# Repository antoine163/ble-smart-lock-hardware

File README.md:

# Bluetooth LE Smart Lock - Hardware

## Cartes électronique
Ce dépôt contient deux cartes :
- **[BleSmartLock](BleSmartLock/README.md)**: La carte principale, construite autour du bluenrg-m2, inclut toute l'électronique de contrôle pour la serrure.
- **[LightSensor](LightSensor/README.md)**: Cette carte contient le capteur de lumière, permettant de le placer à distance. Cette carte est optionnelle.

## Réalisation

### Liste du matérielle:
Cette liste de matériel est disponible sur Amazon.
- [Alimentation 12V](https://www.amazon.fr/dp/B0924XBMCF?ref=ppx_yo2ov_dt_b_fed_asin_title&th=1) pour alimenter la serrure.
- [Serrure électromécanique](https://www.amazon.fr/dp/B07KWMH16C?ref=ppx_yo2ov_dt_b_fed_asin_title) pour la partie électromécanique de la serrure.
- [Bouton lumineux](https://www.amazon.fr/dp/B0CBRFQLLT?ref=ppx_yo2ov_dt_b_fed_asin_title&th=1) pour l'ouverture de la serrure et visualisation de l'état de la serrure.
- [Boîtier étanche](https://www.amazon.fr/dp/B09V7M8759?ref=ppx_yo2ov_dt_b_fed_asin_title) pour recevoir la carte électronique principale *BleSmartLock*.
- [Câble 4 conducteurs](https://www.amazon.fr/dp/B0BFWJ19YJ?ref=ppx_yo2ov_dt_b_fed_asin_title&th=1) pour la connexion entre la carte électronique principale et:
    - La serrure électromécanique
    - Le bouton lumineux
    - L'éclairage d'ambiance
    - Le capteur de lumière
    - L'éclairage extérieur
- [Câble 2 conducteurs](https://www.amazon.fr/dp/B0B7WV1QCW?ref=ppx_yo2ov_dt_b_fed_asin_title) pour l'alimentation.
- [Presse-étoupes](https://www.amazon.fr/dp/B07V7F5HKQ?ref=ppx_yo2ov_dt_b_fed_asin_title&th=1) pour faire passer les différents câbles dans les boîtiers étanches.
- [Boîtier étanche](https://www.amazon.fr/dp/B0BZCS1PN1?ref=ppx_yo2ov_dt_b_fed_asin_title) pour recevoir le capteur de luminosité *LightSensor* et la lampe extérieur *Mini-Light*.
- [Colle epoxy transparent](https://www.amazon.fr/dp/B07JL8JC3N?ref=ppx_yo2ov_dt_b_fed_asin_title) pour réaliser une vitre dans le boîtier du capteur de luminosité et de la lampe extérieur.

### Mise en boiter de la carte principal *BleSmartLock* 

### Mise en boiter de la carte capteur *LightSensor* et lampe extérieur *Mini-Light*
On notera ici que 2 cartes *Mini-Light* ont été utilisées pour augmenter la luminosité de la lampe extérieur.  
**NOTE:** Un maximum de 2 cartes *Mini-Light* peut être utilisé directement à la carte principale *BleSmartLock*.  

Au préalable, il est nécessaire de percer un trou rectangulaire et un trou rond dans le couvercle du boîtier, puis de les remplir de colle époxy transparente. Cela permet de créer des vitres, assurant ainsi le passage de la lumière utile au capteur de luminosité et d'éclairage extérieur.  

## Prototypes
### Avec les cartes v1.0

### Sur plaque d'essai

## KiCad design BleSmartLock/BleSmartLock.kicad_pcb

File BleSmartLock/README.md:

# BleSmartLock Board
Cette carte est la carte principale du projet. Elle est basée sur le module radio Bluenrg-m2 et fais l'interface avec les autres organes, telle que la serrure elle-même et le bouton pour l'ouverture.

Voir le [README](../../Firmware/README.md) du firmware pour la programmation de cette carte.

## Vue 3D

## Réalisation
### Fabrication de la version v1.0
#### Correction
Une erreur c'est glissée à la saisie de la schématique. DIO12 peut seulement être une entrée. la version v1.1 inverse DIO12 avec DIO6.
Il faut inverser c'est deux gpio sur le pcb en coupent deux pistes et en croisent les connections.

#### Photos

#### BOM
La bom interactive est trouvable [ici](https://antoine163.github.io/ble-smart-lock-hardware/Ble_Smart_Lock_1.0-ibom.html). 

### Fabrication de la version v1.1
Je n'est pas fabrique cette version, mais elle dispose exactement des mêmes composent que la v1.0.
La bom interactive est trouvable [ici](https://antoine163.github.io/ble-smart-lock-hardware/Ble%20Smart%20Lock-1.1-ibom.html). 

# Schématique

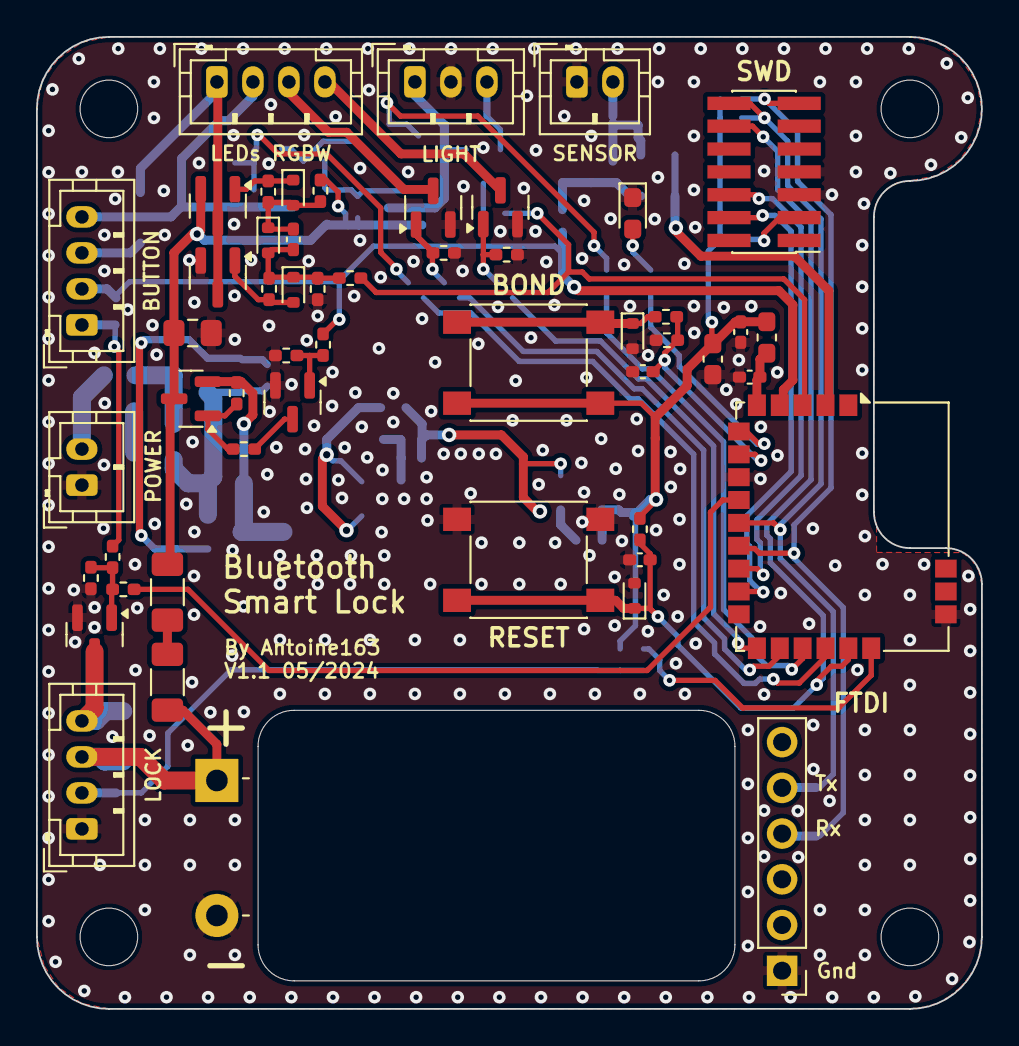
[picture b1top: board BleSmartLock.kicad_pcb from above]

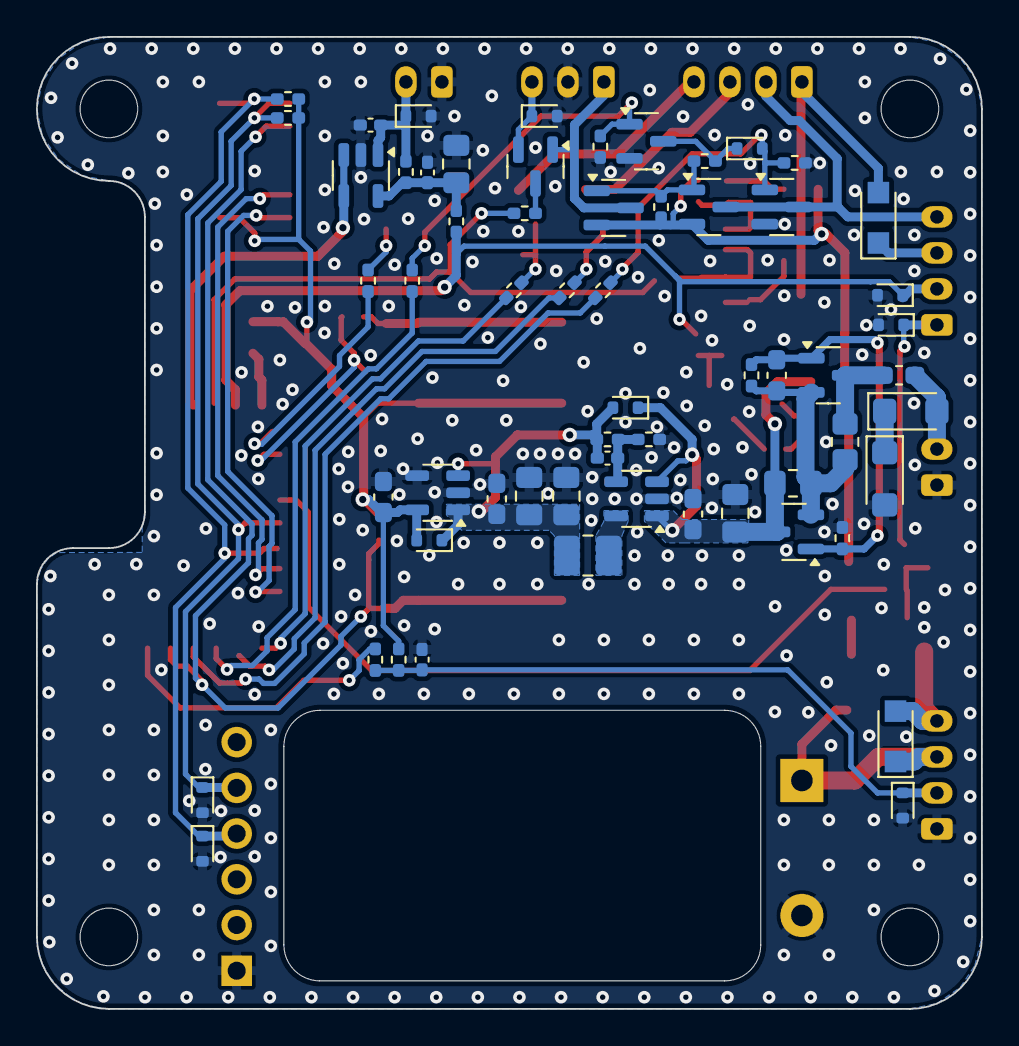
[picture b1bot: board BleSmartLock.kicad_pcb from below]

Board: 2 copper layers, 52.5 x 54.0 mm, 116 parts (60 on the bottom side), 60 nets.

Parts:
C1, C3: 1uF; C_0603_1608Metric_Pad1.08x0.95mm_HandSolder
C2: 470nF; C_0603_1608Metric_Pad1.08x0.95mm_HandSolder
C4, C7, C8, C14, C18: 10uF; C_0805_2012Metric_Pad1.18x1.45mm_HandSolder
C5, C11: 2.2uF; C_0603_1608Metric_Pad1.08x0.95mm_HandSolder
C6: 15pF; C_0402_1005Metric_Pad0.74x0.62mm_HandSolder
C9, C16: 10nF; C_0402_1005Metric_Pad0.74x0.62mm_HandSolder
C10, C12, C13, C17, C19, C20: 100nF; C_0402_1005Metric_Pad0.74x0.62mm_HandSolder
C15: 4700uF; CP_Radial_L25.0mm_D16.0mm_P7.50mm_Horizontal_EdgeCuts
D1, D2: SMF12A; D_SMF
D3, D4, D13, D14, D19: RB501SM-30FH; D_SOD-523
D5, D6, D8, D9, D11, D15, D17, D18, D20: ESD5Z3.3T1G; D_SOD-523
D7: LED; LED_0603_1608Metric_Pad1.05x0.95mm_HandSolder
D10, D16: PMEG40T10ER; Nexperia_CFP3_SOD-123W
D12: EDZVT2R9.1B; D_SOD-523
F1: 1A; L_0603_1608Metric_Pad1.05x0.95mm_HandSolder
H1, H2, H3, H4: MountingHole; MountingHole_3.2mm_M3
J1, J12: Conn_01x02; JST_PH_B2B-PH-K_1x02_P2.00mm_Vertical
J6: Conn_ST_STDC14; PinHeader_2x07_P1.27mm_Vertical_SMD
J7: Conn_01x06; PinHeader_1x06_P2.54mm_Vertical
J8: Conn_01x03; JST_PH_B3B-PH-K_1x03_P2.00mm_Vertical
J9, J10, J11: Conn_01x04; JST_PH_B4B-PH-K_1x04_P2.00mm_Vertical
L1: 10uH; L_1008_2520Metric_Pad1.43x2.20mm_HandSolder
L2: MPZ1608; L_0603_1608Metric_Pad1.05x0.95mm_HandSolder
Q1, Q2, Q4, Q7, Q9, Q11: PMV50UPE; SOT-23
Q3, Q5, Q8, Q10, Q12, Q13, Q14: NX7002AKA; SOT-23
Q6: PMV52ENEA; SOT-23
R1, R4: 0R; R_0805_2012Metric_Pad1.20x1.40mm_HandSolder
R2, R9, R14, R15, R19, R21, R25, R29, R30, R31, R32, R35, R37, R39: 100K; R_0402_1005Metric_Pad0.72x0.64mm_HandSolder
R3, R24, R27: 470K; R_0402_1005Metric_Pad0.72x0.64mm_HandSolder
R5: 910K; R_0402_1005Metric_Pad0.72x0.64mm_HandSolder
R6: 240K; R_0402_1005Metric_Pad0.72x0.64mm_HandSolder
R7: 47K; R_0402_1005Metric_Pad0.72x0.64mm_HandSolder
R8, R10, R13, R17, R18, R23, R28, R33, R34, R36, R38, R40: 1K; R_0402_1005Metric_Pad0.72x0.64mm_HandSolder
R11, R12, R20: 10K; R_0402_1005Metric_Pad0.72x0.64mm_HandSolder
R16, R22: 100R; R_1206_3216Metric_Pad1.30x1.75mm_HandSolder
R26: 0R; R_0402_1005Metric_Pad0.72x0.64mm_HandSolder
R41: 160K; R_0402_1005Metric_Pad0.72x0.64mm_HandSolder
SW1, SW2: SW_Push; SW_SPST_PTS645
U1: RT9086; SOT-23-5
U2: XC9264b755; SOT-23-5
U3: BLUENRG-M2SA
U4: LMV611; SOT-23-5

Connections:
+3V3: C3.1, C11.1, C12.1, D3.2 (A), J6.3 (VCC), L2.1, R7.1, R11.1, R12.1, R29.2, SW2.1, U1.5 (VOUT)
+12V: C4.1, C5.1, D4.1 (K), Q2.3 (D), Q4.2 (S), R4.2, R14.1, U2.1 (Vin), U2.3 (EN/SS)
/Bluenrg/BOND: C10.1, R8.2, R9.1, U3.7 (DIO7/BOOT)
/Bluenrg/BRIGHTNESS: U3.2 (ADC1), U4.3 (-), U4.4
/Bluenrg/EN_IO: D15.1 (K), J9.2, R13.1, R34.1, U3.4 (DIO5)
/Bluenrg/LED: R10.1, U3.6 (ANATEST0/DIO14)
/Bluenrg/LIGHT_BLUE: R33.1, U3.18 (DIO1)
/Bluenrg/LIGHT_GREEN: R40.2, U3.16 (DIO2)
/Bluenrg/LIGHT_PWM: R17.1, R23.1, U3.3 (DIO4)
/Bluenrg/LIGHT_RED: R38.1, U3.15 (DIO0)
/Bluenrg/LIGHT_WHITE: R36.1, U3.17 (DIO3)
/Bluenrg/M2_SWDCLK: J6.6 (JCLK/SWCLK), U3.12 (DIO9)
/Bluenrg/M2_SWDIO: J6.4 (JTMS/SWDIO), U3.13 (DIO10)
/Bluenrg/M2_~RESET: C9.1, D5.1 (K), J6.12 (~RST), R7.2, SW1.1, U3.19 (~RESET)
/Bluenrg/OPENED: R28.1, U3.20 (DIO12)
/Bluenrg/UART_RX: D9.1 (K), J6.13 (VCP_RX), J7.4, R12.2, U3.11 (DIO11)
/Bluenrg/UART_TX: D8.1 (K), J6.14 (VCP_TX), J7.5, R11.2, U3.10 (DIO8)
/Bluenrg/~LOCK: R18.1, U3.9 (DIO6)
/InOut/AM_LIGHT_12V_W-: D16.2 (A), J11.1, Q7.3 (D), Q8.3 (D)
/InOut/AM_LIGHT_B_W+: J9.4, J11.2, Q9.3 (D), Q10.3 (D)
/InOut/AM_LIGHT_G: J11.3, Q14.3 (D)
/InOut/AM_LIGHT_POWER: J8.1, Q5.1 (G), Q11.3 (D)
/InOut/AM_LIGHT_R: J11.4, Q13.3 (D)
/InOut/BP_LED_P: D16.1 (K), J9.3
/InOut/BP_NO: D18.1 (K), J9.1, R20.1
/InOut/COIL_N: D10.2 (A), J10.4, Q6.3 (D)
/InOut/COIL_P: C15.1, D10.1 (K), J10.3, R22.2
/InOut/EX_LIGHT_CMD: D11.1 (K), J8.3, Q5.2 (S)
/InOut/POWER_IO_12V: C14.1, Q4.3 (D), Q7.2 (S), Q9.2 (S), Q11.2 (S), R16.1, R24.1, R30.1
/Power/3V6: C1.2, C6.1, C7.1, C8.1, D3.1 (K), D4.2 (A), L1.2, R5.1, U1.1 (VIN), U1.3 (EN)
GND: C1.1, C3.2, C4.2, C5.2, C7.2, C8.2, C9.2, C10.2, C11.2, C12.2, C13.2, C14.2, C15.2, C17.2, C18.2, C19.2, C20.2, D2.2 (A2), D5.2 (A), D6.2 (A), D7.1 (K), D8.2 (A), D9.2 (A), D11.2 (A), D15.2 (A), D17.2 (A), D18.2 (A), D20.2 (A), J1.1, J6.5 (GND), J6.7 (GND), J7.1, J8.2, J10.1, J12.1, Q3.2 (S), Q6.2 (S), Q8.2 (S), Q10.2 (S), Q12.2 (S), Q13.2 (S), Q14.2 (S), R3.2, R6.2, R9.2, R15.2, R21.2, R25.2, R32.2, R35.2, R37.2, R39.2, SW1.2, U1.2 (GND), U1.4 (NC), U2.2 (GND), U3.8 (GND), U3.21 (GND), U4.2 (V-)
unnamed: D1.1 (A1), D2.1 (A1)
unnamed: D1.2 (A2), F1.1, J1.2
unnamed: D6.1 (K), R8.1, SW2.2
unnamed: D7.2 (A), R10.2
unnamed: C16.2, D12.2 (A), D14.1 (K), R23.2, R25.1, R27.1
unnamed: C16.1, D12.1 (K), D13.2 (A), R24.2, R26.1
unnamed: D13.1 (K), Q7.1 (G), R26.2
unnamed: D14.2 (A), Q8.1 (G), R27.2
unnamed: C17.1, D17.1 (K), J10.2, R28.2, R29.1
unnamed: D19.2 (A), Q10.1 (G), R32.1, R33.2
unnamed: D19.1 (K), Q12.3 (D), R31.2
unnamed: C20.1, D20.1 (K), J12.2, R41.2, U4.1 (+)
unnamed: F1.2, Q1.3 (D), R1.1
unnamed: C2.2, Q1.1 (G), Q2.1 (G), R2.2, R3.1
unnamed: C2.1, Q1.2 (S), Q2.2 (S), R1.2, R2.1, R4.1
unnamed: Q3.3 (D), R19.2
unnamed: Q3.1 (G), R13.2, R15.1
unnamed: Q4.1 (G), R14.2, R19.1
unnamed: Q5.3 (D), R17.2
unnamed: Q6.1 (G), R18.2, R20.2, R21.1
unnamed: Q9.1 (G), Q11.1 (G), R30.2, R31.1
unnamed: Q12.1 (G), R35.1, R36.2
unnamed: Q13.1 (G), R37.1, R38.2
unnamed: Q14.1 (G), R39.1, R40.1
unnamed: R16.2, R22.1
unnamed: C6.2, R5.2, R6.1, U2.4 (FB)
unnamed: L1.1, U2.5 (Lx)
unnamed: C13.1, L2.2, U3.5 (VIN)
unnamed: C18.1, C19.1, R34.2, R41.1, U4.5 (V+)

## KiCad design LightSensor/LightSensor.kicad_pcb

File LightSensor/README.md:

# BleSmartLock-LightSensor Board
C'est la carte satellite permettant de déporter le capteur de luminosité. Elle est constituée principalement du capteur KPS-3227.

## Vue 3D

## Réalisation
### Fabrication de la version v1.0
#### Photos

#### BOM
Cette carte est constituée seulement d'un connecteur JST et du capteur de lumière ambiante:
- JST: [B2B-PH-K-S](https://www.amazon.fr/gp/product/B0731MZCGF/ref=ppx_yo_dt_b_asin_title_o02_s00?ie=UTF8&psc=1).
- KINGBRIGHT: [KPS-3227SP1C](https://fr.farnell.com/kingbright/kps-3227sp1c/capteur-optique-phototransistor/dp/2373478). 

### Fabrication de la version v1.1
Je n'est pas fabrique cette version, seulement le connecteur à été tournée de 180 degrés.

# Schématique

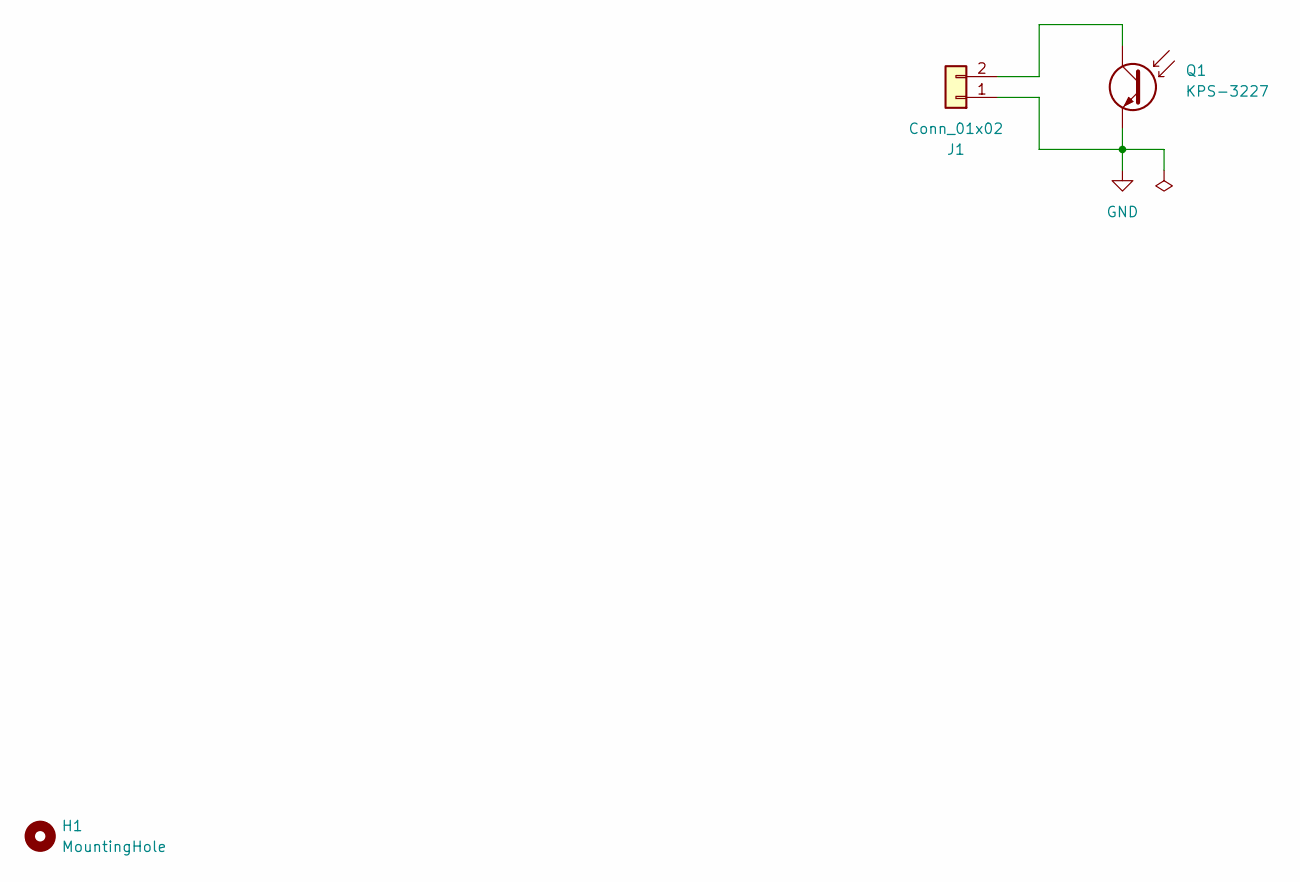
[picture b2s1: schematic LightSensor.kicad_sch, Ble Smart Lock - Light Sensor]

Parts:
H1: MountingHole; MountingHole_3.2mm_M3
J1: Conn_01x02; JST_PH_B2B-PH-K_1x02_P2.00mm_Vertical
Q1: KPS-3227; Kingbright_KPS-3227

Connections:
GND: J1.1, Q1.2, Q1.4
unnamed: J1.2, Q1.1, Q1.3

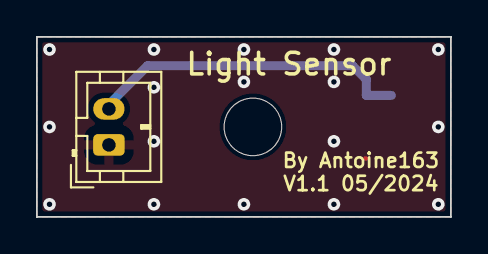
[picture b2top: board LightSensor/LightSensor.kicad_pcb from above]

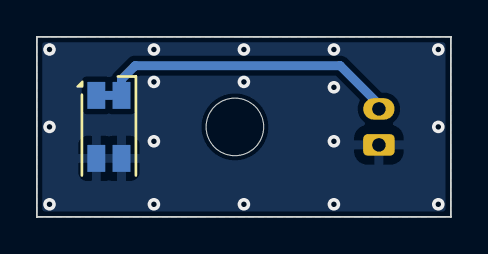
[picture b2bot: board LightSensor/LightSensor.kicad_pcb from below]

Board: 2 copper layers, 23.0 x 10.0 mm, 3 parts (2 on the bottom side), 2 nets.

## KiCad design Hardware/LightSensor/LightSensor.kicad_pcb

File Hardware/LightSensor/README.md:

# BleSmartLock-LightSensor Board
C'est la carte satellite permettant de déporter le capteur de luminosité. Elle est constituée principalement du capteur KPS-3227.

## Vue 3D

# Schématique

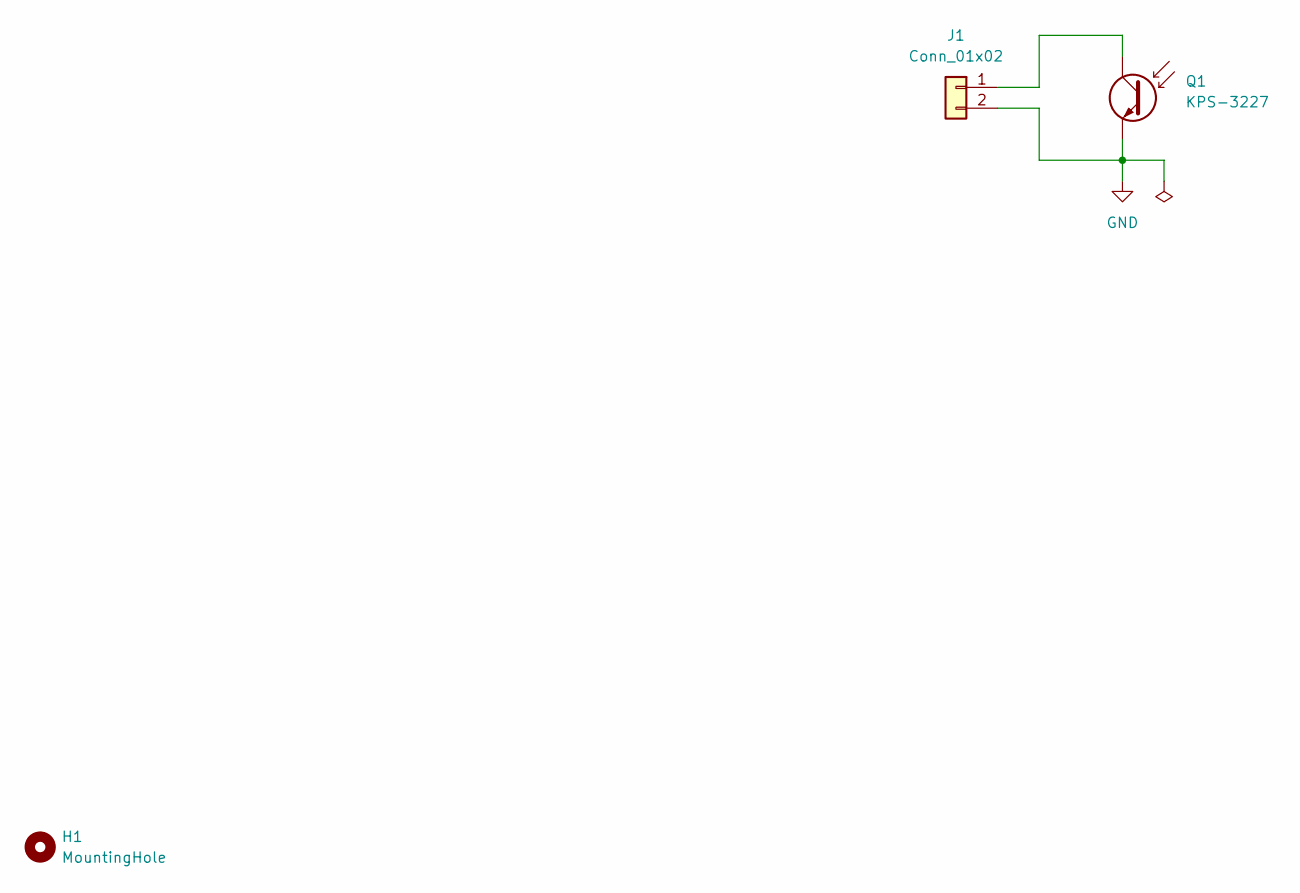
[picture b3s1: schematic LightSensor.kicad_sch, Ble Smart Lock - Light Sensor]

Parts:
H1: MountingHole; MountingHole_3.2mm_M3
J1: Conn_01x02; JST_PH_B2B-PH-K_1x02_P2.00mm_Vertical
Q1: KPS-3227; Kingbright_KPS-3227

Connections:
GND: J1.2, Q1.2, Q1.4
unnamed: J1.1, Q1.1, Q1.3

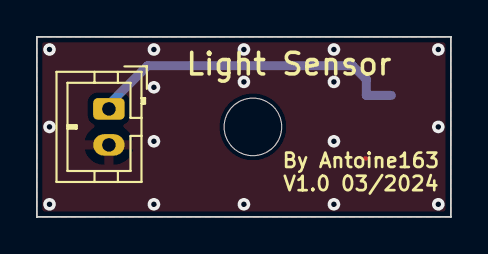
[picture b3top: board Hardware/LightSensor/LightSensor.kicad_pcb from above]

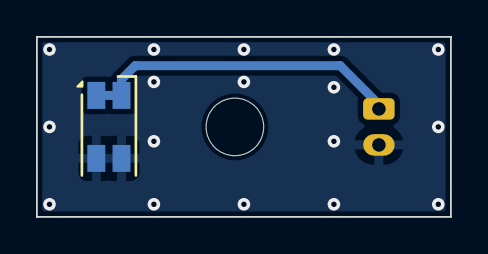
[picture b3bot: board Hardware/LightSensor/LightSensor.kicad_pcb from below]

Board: 2 copper layers, 23.0 x 10.0 mm, 3 parts (2 on the bottom side), 2 nets.

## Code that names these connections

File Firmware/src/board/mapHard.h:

/***
 * The MIT License (MIT)
 *
 * Copyright (c) 2023 antoine163
 *
 * Permission is hereby granted, free of charge, to any person obtaining a copy
 * of this software and associated documentation files (the "Software"), to deal
 * in the Software without restriction, including without limitation the rights
 * to use, copy, modify, merge, publish, distribute, sublicense, and/or sell
 * copies of the Software, and to permit persons to whom the Software is
 * furnished to do so, subject to the following conditions:
 *
 * The above copyright notice and this permission notice shall be included in all
 * copies or substantial portions of the Software.
 *
 * THE SOFTWARE IS PROVIDED "AS IS", WITHOUT WARRANTY OF ANY KIND, EXPRESS OR
 * IMPLIED, INCLUDING BUT NOT LIMITED TO THE WARRANTIES OF MERCHANTABILITY,
 * FITNESS FOR A PARTICULAR PURPOSE AND NONINFRINGEMENT. IN NO EVENT SHALL THE
 * AUTHORS OR COPYRIGHT HOLDERS BE LIABLE FOR ANY CLAIM, DAMAGES OR OTHER
 * LIABILITY, WHETHER IN AN ACTION OF CONTRACT, TORT OR OTHERWISE, ARISING FROM,
 * OUT OF OR IN CONNECTION WITH THE SOFTWARE OR THE USE OR OTHER DEALINGS IN THE
 * SOFTWARE.
 */

#ifndef BOARD_IO_H
#define BOARD_IO_H

// IN
#define BOND_PIN                GPIO_Pin_7
#define BOND_MODE               GPIO_Input
#define OPENED_PIN              GPIO_Pin_12
#define OPENED_MODE             GPIO_Input

// IN/OUT
#define LOCK_PIN                GPIO_Pin_6
#define LOCK_MODE_OUT           GPIO_Output
#define LOCK_MODE_IN            GPIO_Input

// OUT
#define LED_PIN                 GPIO_Pin_14
#define LED_MODE                GPIO_Output

#define EN_IO_PIN               GPIO_Pin_5
#define EN_IO_MODE              GPIO_Output

// LIGHT
#define LIGHT_RED_PIN           GPIO_Pin_0
#define LIGHT_BLUE_PIN          GPIO_Pin_1
#define LIGHT_GREEN_PIN         GPIO_Pin_2
#define LIGHT_WHITE_PIN         GPIO_Pin_3
#define LIGHT_MODE              GPIO_Output

#define LIGHT_PWM_PIN           GPIO_Pin_4
#define LIGHT_PWM_MODE_OUT      GPIO_Output
#define LIGHT_PWM_MODE_PWM      Serial2_Mode

// UART
#define UART_RX_PIN             GPIO_Pin_11
#define UART_RX_MODE            Serial1_Mode
#define UART_RX_FIFO_SIZE       32

#define UART_TX_PIN             GPIO_Pin_8
#define UART_TX_MODE            Serial1_Mode
#define UART_TX_FIFO_SIZE       1024

#endif // BOARD_IO_H

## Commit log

2024-01-27 readme de description du project
2024-02-18 Ajout des fichiers kicad.
2024-02-24 [firm] Ajout des premier fichiers compilable
2024-02-24 [firm] Mise a jour du readme
2024-03-16 Re-organisation des dossiers (déplacement du kicad BleSmartLock et du firmware)
2024-03-16 ajout carte LightSensor
2024-03-30 Ajout carte BleSmartLock
2024-03-30 Ajout fichier de production et bom interactive
2024-03-31 ibon Ble_Smart_Lock 1.0
2024-03-31 Déplace ibom dans gh-pages
2024-03-31 Déplace les images dans le dossier images
2024-03-31 maj .gitignore
2024-03-31 Ajout fichier de production de la carte LightSensor
2024-04-01 Ajustement pour prendre en compte les dernières modifications hardware.
2024-04-01 [firm] ajour freertos v11.0.1 en sous module
2024-04-01 [firm] Remise en place de l'uart
2024-04-04 [firm] Mise en place rapide de la tache ble
2024-04-06 [firm] Driver pwm
2024-04-09 [firm] amelioration du pilotage des leds
2024-04-11 [firm] Implementation de taskLightSetColor() et simplification temporaire de la tache light
2024-04-13 Implementation de boardGetBrightness() / ADC
2024-04-13 Ajout des fonctions 'board' pour verrouiller/déverrouiller et ouvrier la serrure
2024-04-19 Envoie un message à la tache App suit à l'appuis sur le bouton Bond
2024-04-28 Configuration de ta stack BLE avec 1 service et 5 caractéristiques
2024-05-01 Renommage des msg en event et init des taches
2024-05-01 Allume en rouge si erreur Ble
2024-05-01 Implementation des différents état de la serrure
2024-05-01 Update brightness char att
2024-05-01 Prise en comte du seuil de luminosité pour allumer ou pas la lumière extérieur.
2024-05-01 Ajout des couleurs et un manager de couleur dans la tache App
2024-05-03 Implement la tache light pour gérer les animations lumineuse
2024-05-05 Débogage et améliore les animations lumineuse
2024-05-05 Correction flache lumineux au changement de couleur
2024-05-06 Petite correction de bug au démarrage de clignotement
2024-05-06 Aller plus proche du dc 0 dans boardSetLightDc
2024-05-06 Allume la lumière externe suite à l'ouverture via la clef même sur le ble est déconnecter.
2024-05-06 Pilotage de EN_IO en fonction du besoin
2024-05-06 Ne pas fair de pub BLE si la porte est ouvert au boot
2024-05-06 Petit mise à jour du readme + comportement led rouge
2024-05-06 Éteint les lumières d'ambience si plus d’activité + reset sui a une erreur.
2024-05-06 Correction de bug sur les transitoires de même couleur.
2024-05-09 Gross revue de la tache BLE permettent l’appairage (il reste encore quelque zone brouillon)
2024-05-18 Suppression des devices liers suit appuis long sur le bouton bond. implementation de taskBleUpdateAtt. Gestion de la liste blanche.
2024-05-18 ibon Ble_Smart_Lock 1.1
2024-05-19 Mise a jour pcb en v1.1 et readme
2024-05-19 Numéro de version depuis le dernier hash git
2024-05-19 Renommage 'action' en 'flag' dans la tache ble et mise à jour des de la luminosité suit demande ble
2024-05-19 Mise a jour de l'attribue BLE en fonction de l’état de la port.
2024-05-19 mise a jour readme
2024-05-20 Réorganise le scrip de lien pour à jouter une section NVM2 et nettoyer les sections OTA inutile ici?
2024-05-20 Écriture/lecture des données de l'app depuis la flash
2024-05-20 Nettoyage
2024-05-20 Utiliser des flags dans la tach app plu que des actions. + Ammonisation
2024-05-25 Restart following a whitelist cleanup.
2024-05-25 PIN depuis la flash
2024-05-25 Ajout boardDgb + squelette de la tache term
2024-05-25 fixbug dans boardDgb
2024-05-26 Ajout tache term + cmd help et version
2024-05-26 fixbug in uart
2024-05-26 formatage
2024-06-01 Ajour la commande top pour afficher le status des taches
2024-06-01 Cmd Verbose
2024-06-01 cmd pin
2024-06-01 cmd bri
2024-06-01 cmd bri-th
2024-06-01 cmd Config
2024-06-01 cmd Bonded
2024-06-01 Correction cmd bonded
2024-06-01 SC_Support a SC_IS_SUPPORTED
2024-06-01 Active TICKLESS_IDLE
2024-06-08 Ajout function uart_waitWrite
2024-06-08 Ajout le handler hard fauld
2024-06-08 Ajuste la taille des taches
2024-06-08 Active le mode deep sleep
2024-06-09 Réveille à l'ouverture de la porte
2024-06-09 Activation du wdg
2024-06-09 Ajout des régles cgdb et load
2024-06-09 Mise a jour du readme du Firmware
2024-06-09 Première version du firmware v1.0.0
2024-08-08 Fix : Correction du comportement du paramètre 'verbose' dans la fonction _taskTermCmdVerbose() pour qu'il désactive effectivement l'affichage des informations détaillées lorsqu'on spécifie 'disable' 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
2024-08-08 Corrigé une erreur d'orthographe dans la fonction taskAppOpenDoor() : foor -> Door
2024-10-12 Separation du hardware du depo principale
2024-10-12 Suppression du .gitmodules
2024-10-13 maj readme
